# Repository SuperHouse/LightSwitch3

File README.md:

Home Automation Light Switch (3 Button)
========================================
Copyright 2014-2017 SuperHouse Automation Pty Ltd  
SuperHouse site:  <www.superhouse.tv>  

Illuminated push button breakout with an RJ45 socket, for mounting
in a wall panel as part of a home automation system.

Features:

 * 3 Illuminated push buttons
 * RJ45 breakout to allow connecting using Cat-5 cable

More information is available at:

  http://www.superhouse.tv/lightswitch

INSTALLATION
------------
The design is saved as an EAGLE project. EAGLE PCB design software is
available from www.cadsoftusa.com free for non-commercial use. To use
this project download it and place the directory containing these files
into the "eagle" directory on your computer. Then open EAGLE and
navigate to the project.

DISTRIBUTION
------------
The specific terms of distribution of this project are governed by the
license referenced below.

LICENSE
-------
Licensed under the TAPR Open Hardware License (www.tapr.org/OHL).
The "license" folder within this repository also contains a copy of
this license in plain text format.

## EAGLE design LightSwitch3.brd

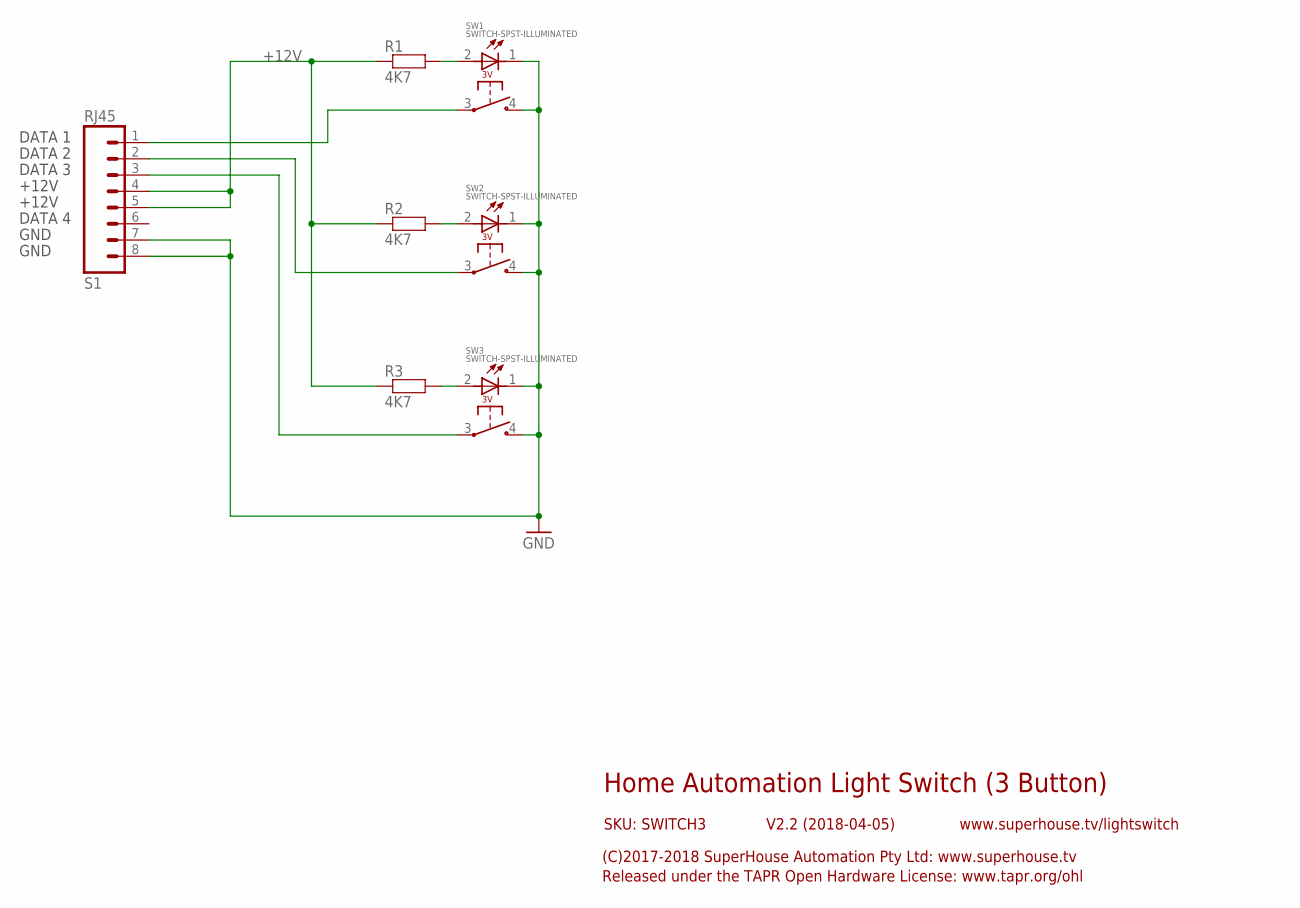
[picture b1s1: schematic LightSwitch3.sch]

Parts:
R1, R2, R3: 4K7; 0603
S1: RJ45
SW1, SW2, SW3: SWITCH-SPST-ILLUMINATED

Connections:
+12V: R1.1, R2.1, R3.1, S1.4, S1.5
GND: S1.7, S1.8, SW1.1 (-), SW1.4 (NO), SW2.1 (-), SW2.4 (NO), SW3.1 (-), SW3.4 (NO)
unnamed: R1.2, SW1.2 (+)
unnamed: S1.3, SW3.3 (COM)
unnamed: R2.2, SW2.2 (+)
unnamed: S1.1, SW1.3 (COM)
unnamed: S1.2, SW2.3 (COM)
unnamed: R3.2, SW3.2 (+)

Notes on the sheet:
Home Automation Light Switch (3 Button)
V2.2 (2018-04-05)
SKU: SWITCH3
(C)2017-2018 SuperHouse Automation Pty Ltd: www.superhouse.tv
Released under the TAPR Open Hardware License: www.tapr.org/ohl
www.superhouse.tv/lightswitch
DATA 1
DATA 2
DATA 3
DATA 4
+12V
GND

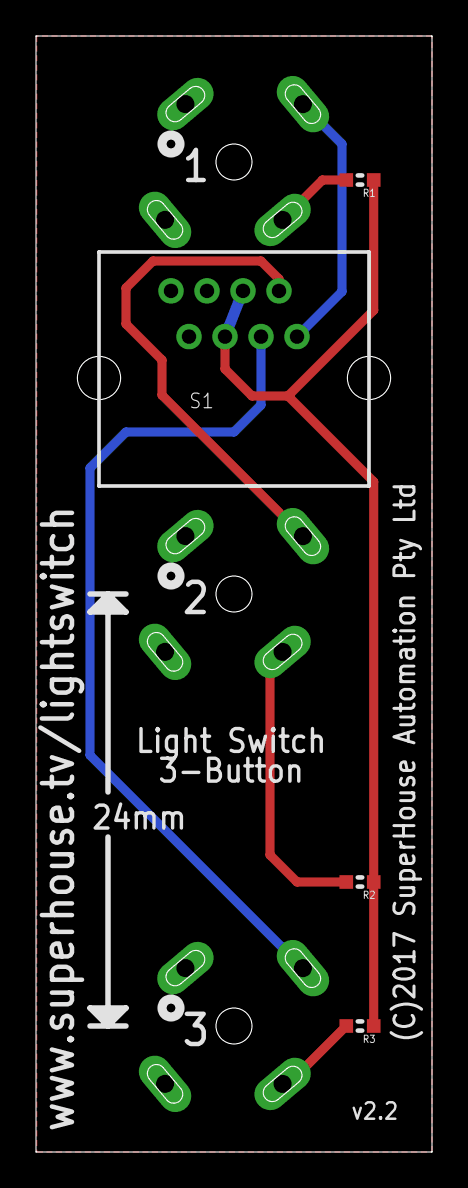
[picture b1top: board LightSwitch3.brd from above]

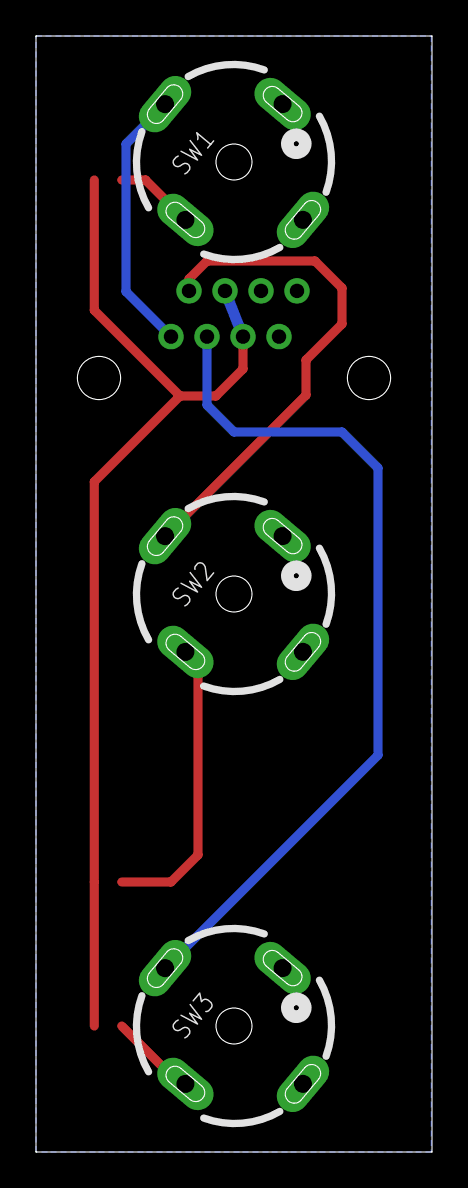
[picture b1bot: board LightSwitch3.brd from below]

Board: 2 copper layers, 22.0 x 62.0 mm, 7 parts (3 on the bottom side), 8 nets.

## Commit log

2017-10-07 Initial project import
2017-10-07 Renamed files
2017-10-07 Fixed README
2017-10-07 Improved labels for clarity
2017-10-07 Replaced buttons with more common SPST type
2017-10-12 Final tweaks preparing for v2.0 release
2018-03-26 Changed button footprint to slotted version for v2.1 release
2018-04-05 Updated RJ45 footprint for v2.2
2020-05-27 Applied SuperHouse design rules

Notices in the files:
LightSwitch3.brd:
(C)2017 SuperHouse Automation Pty Ltd
